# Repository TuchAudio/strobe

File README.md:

# strobe
Handy 50 Hz stroboscope

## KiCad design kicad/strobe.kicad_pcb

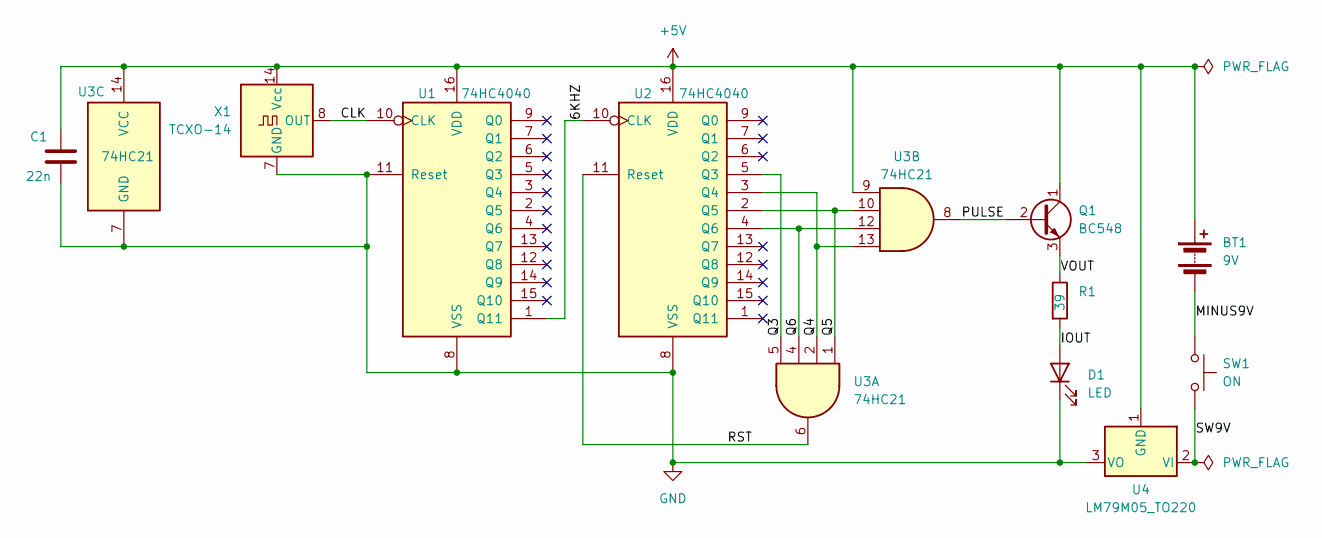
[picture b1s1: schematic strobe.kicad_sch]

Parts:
BT1: 9V; PinHeader_1x02_P2.54mm_Horizontal
C1: 22n; C_Disc_D6.0mm_W2.5mm_P5.00mm
D1: LED; LED_D3.0mm_Horizontal_O3.81mm_Z10.0mm
Q1: BC548; TO-92_Inline
R1: 39; R_Axial_DIN0207_L6.3mm_D2.5mm_P10.16mm_Horizontal
SW1: ON; SW_PUSH_6mm
U1, U2: 74HC4040; DIP-16_W7.62mm
U3: 74HC21; DIP-14_W7.62mm
U4: LM79M05_TO220; TO-220-3_Vertical
X1: TCXO-14; Oscillator_DIP-14

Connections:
+5V: BT1.1 (+), C1.1, Q1.1 (C), U1.16 (VDD), U2.16 (VDD), U3.9, U3.14 (VCC), U4.1 (GND), X1.14 (Vcc)
/6KHZ: U1.1 (Q11), U2.10 (CLK)
/CLK: U1.10 (CLK), X1.8 (OUT)
/IOUT: D1.2 (A), R1.2
/MINUS9V: BT1.2 (-), SW1.1
/PULSE: Q1.2 (B), U3.8
/Q3: U2.5 (Q3), U3.5
/Q4: U2.3 (Q4), U3.2, U3.13
/Q5: U2.2 (Q5), U3.1, U3.10
/Q6: U2.4 (Q6), U3.4, U3.12
/RST: U2.11 (Reset), U3.6
/SW9V: SW1.2, U4.2 (VI)
/VOUT: Q1.3 (E), R1.1
GND: C1.2, D1.1 (K), U1.8 (VSS), U1.11 (Reset), U2.8 (VSS), U3.7 (GND), U4.3 (VO), X1.7 (GND)

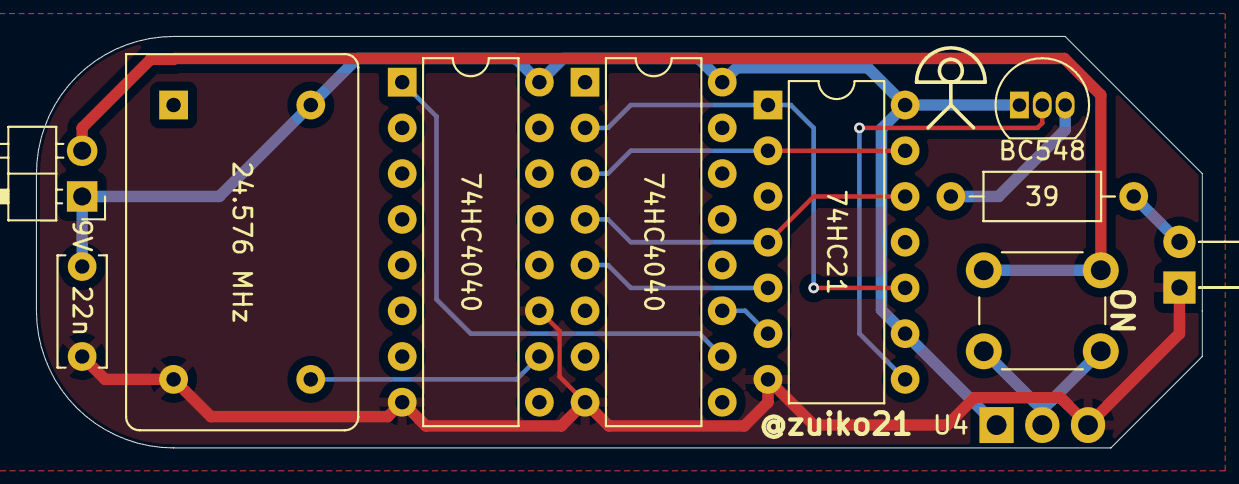
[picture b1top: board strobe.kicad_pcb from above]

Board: 2 copper layers, 64.8 x 22.9 mm, 11 parts (1 on the bottom side), 14 nets.

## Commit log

2025-11-08 add KiCAD files
